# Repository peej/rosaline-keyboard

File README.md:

# Rosaline - Through-hole 40% keyboard PCB for 60% cases

Rosaline is a 40% keyboard PCB using through-hole components for that visible component aesthetic.

The goal of this project is to build an all through-hole component 40% PCB that fits in a standard 60% tray mount case.

Inspired by the [Plaid](https://github.com/hsgw/plaid) and the [Romeo](https://github.com/coseyfannitutti/romeo).

* Designed to be easy to build with minimal soldering experience.
* All through-hole components, no SMD soldering required.
* Get that visible component aesthetic in a standard 60% tray-mount case.
* Staggered and ortholinear varieties.
* Supports both USB Mini and USB-C.

The layout is a number row-less 60% layout with split spacebar or 7u bottom row and split right shift. An arrow cluster layout is also supported by moving the right shift.

# Ordering parts

PCBs can be manufactuered by a variety of online PCB fabricators. You can use [PCBShopper](https://pcbshopper.com/) to search for the best price.

# Construction

Solder all the components onto the top side of the PCB except the USB connector which should be on the back of the board. Leave the larger components until last so that the board will lie flat upsidedown while you solder the resistors and capacitors.

Take care to put the correct value resistors and capacitors in the correct places, the values are written on the silkmask along with the component reference. If you are unsure about the value of a resistor, check it with a multimeter.

Ensure that polarised components (diodes, LEDs, electrolytic capacitor (C3), IC socket) are in the correct orientation. The square pad is for the negative side of the component; for a diode this means the side with the black stripe; for LEDs and C3 the short leg is the cathode and goes in the square pad.

# Firmware

Firmware has not been merged into QMK upstream as of yet.

## Matrix information

If you are building your own firmware, the following matrix information will be useful to you:

| Configuration   | Value                                  |
|-----------------|----------------------------------------|
| MATRIX_ROWS     | 7                                      |
| MATRIX_COLS     | 8                                      |
| MATRIX_ROW_PINS | C0, B5, B4, B3, B2, B1, C3             |
| MATRIX_COL_PINS | B0, D7, D6, C2, D4, D1, D0, C1         |
| DIODE_DIRECTION | COL2ROW                                |

# Component cover

Cut a piece of 2mm thick acrylic to size (285x19mm) and drill 3 m2 holes for the standoffs. Use the PCB as a guide for the hole positions.

Affix the 3 standoffs to the PCB with screws from underneath the PCB. Use the remaining 3 screws to attach the acrylic to the top of the standoffs.

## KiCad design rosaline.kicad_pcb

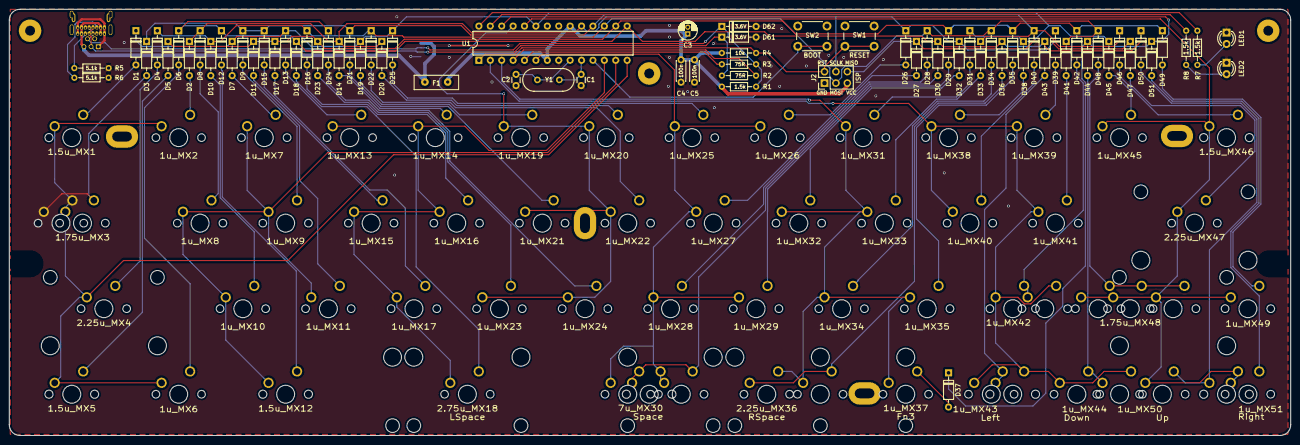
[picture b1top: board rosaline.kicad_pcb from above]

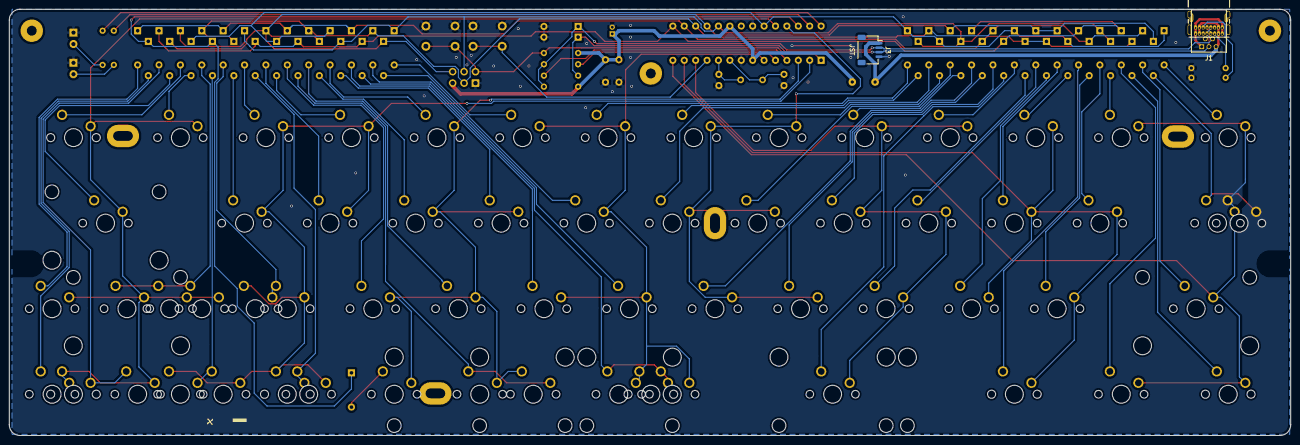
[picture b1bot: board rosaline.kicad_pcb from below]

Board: 2 copper layers, 285.4 x 94.9 mm, 148 parts (3 on the bottom side), 83 nets.

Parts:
1.5u_MX1: Tab; MX_PCB_150H
1.5u_MX5: LCtrl; MX_PCB_150H
1.5u_MX12: LAlt; MX_PCB_150H
1.5u_MX43: RAlt; MX_PCB_150H
1.5u_MX46: Back; MX_PCB_150H
1.5u_MX50: RCtrl; MX_PCB_150H
1.75u_MX3: Esc; MX_PCB_175H
1.75u_MX42, 1.75u_MX48: RShift; MX_PCB_175H
1u2_MX44: RGui; MX
1u_MX2: Q; MX
1u_MX6: LGui; MX
1u_MX7: W; MX
1u_MX8: A; MX
1u_MX9: S; MX
1u_MX10: Z; MX
1u_MX11: X; MX
1u_MX13: E; MX
1u_MX14: R; MX
1u_MX15: D; MX
1u_MX16, 1u_MX21: F; MX
1u_MX17: C; MX
1u_MX19: T; MX
1u_MX20: Y; MX
1u_MX22: G; MX
1u_MX23: V; MX
1u_MX24: B; MX
1u_MX25: U; MX
1u_MX26: I; MX
1u_MX27: J; MX
1u_MX28: N; MX
1u_MX29: M; MX
1u_MX30, 1u_MX36: Fn2; MX
1u_MX31: O; MX
1u_MX32: K; MX
1u_MX33: L; MX
1u_MX34: ,; MX
1u_MX35: .; MX
1u_MX37: Fn3; MX
1u_MX38: P; MX
1u_MX39: [; MX
1u_MX40: ;; MX
1u_MX41: '; MX
1u_MX42: /; MX
1u_MX43: Left; MX
1u_MX44: Down; MX
1u_MX45: ]; MX
1u_MX48, 1u_MX50: Up; MX
1u_MX49: Fn; MX
1u_MX51: Right; MX
2.25u_MX4: LShift; MX_PCB_225H
2.25u_MX30, 2.25u_MX36: RSpace; MX_PCB_225B
2.25u_MX47: Enter; MX_PCB_225H
2.75u_MX18: LSpace; MX_PCB_275B
2.75u_MX48: RShift; MX_PCB_275H
7u_MX30: Space; MX_PCB_700H
C1, C2: 22p; C_Disc_D3.0mm_W1.6mm_P2.50mm
C3: 4.7u; CP_Radial_D4.0mm_P1.50mm
C4, C5: 100n; C_Disc_D4.3mm_W1.9mm_P5.00mm
D1, D2, D3, D4, D5, D6, D7, D8, D9, D10, D11, D12, D13, D14, D15, D16, D17, D18, D19, D20, D21, D22, D23, D24, D25, D26, D27, D28, D29, D30, D31, D32, D33, D34, D35, D36, D37, D38, D39, D40, D41, D42, D43, D44, D45, D46, D47, D48, D49, D50, D51: 1N4148; D_DO-35_SOD27_P7.62mm_Horizontal
D61, D62: 3.6V; D_DO-35_SOD27_P7.62mm_Horizontal
F1: 100mA; Fuse_Bourns_MF-RHT100
Flags: flags; Flags
H1, H2, H3: M2; MountingHole_M2
H4, H9: M2; MountingSlot_M2
H5, H6, H7, H8: M2; MountingFlex_M2
J1: USB; USB_Hybrid_THT
J2: AVR_ISP_6; PinHeader_2x03_P2.54mm_Vertical
J3: JST; JST_SH_SM04B-SRSS-TB_1x04-1MP_P1.00mm_Horizontal
LED1: RED; LED_D3.0mm
LED2: GREEN; LED_D3.0mm
OSHW: OSHW-Logo_7.5x8mm_Copper
R1, R7, R8: 1.5k; R_Axial_DIN0204_L3.6mm_D1.6mm_P7.62mm_Horizontal
R2, R3: 75R; R_Axial_DIN0204_L3.6mm_D1.6mm_P7.62mm_Horizontal
R4: 10k; R_Axial_DIN0204_L3.6mm_D1.6mm_P7.62mm_Horizontal
R5, R6: 5.1k; R_Axial_DIN0204_L3.6mm_D1.6mm_P7.62mm_Horizontal
SW1: RESET; SW_PUSH_6mm
SW2: BOOT; SW_PUSH_6mm
U1: ATMEGA328-PU; DIP-28_W7.62mm
Y1: 16MHz; Crystal_HC49-4H_Vertical
stepped_MX3: Esc; MX

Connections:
+5V: C3.1, C4.1, C5.1, F1.2, J2.5, R1.2, R4.1, U1.7, U1.20
/COL0: 1.5u_MX1.2, 1.5u_MX5.2, 1.75u_MX3.2, 1u_MX2.2, 1u_MX6.2, 2.25u_MX4.2, U1.14, stepped_MX3.1
/COL1: 1.5u_MX12.2, 1u_MX7.2, 1u_MX8.2, 1u_MX9.2, 1u_MX10.2, 1u_MX11.2, U1.13
/COL2: 1u_MX13.2, 1u_MX14.2, 1u_MX15.2, 1u_MX16.2, 1u_MX17.2, 2.75u_MX18.2, U1.12
/COL3: 1u_MX19.2, 1u_MX20.2, 1u_MX21.2, 1u_MX22.2, 1u_MX23.2, 1u_MX24.2, U1.25
/COL4: 1u_MX25.2, 1u_MX26.2, 1u_MX27.2, 1u_MX28.2, 1u_MX29.2, 1u_MX30.2, 2.25u_MX30.2, 7u_MX30.1, U1.6
/COL5: 1u_MX31.2, 1u_MX32.2, 1u_MX33.2, 1u_MX34.2, 1u_MX35.2, 1u_MX36.2, 1u_MX37.2, 2.25u_MX36.1, U1.3
/COL6: 1.5u_MX43.1, 1.75u_MX42.1, 1u2_MX44.1, 1u_MX38.2, 1u_MX39.2, 1u_MX40.2, 1u_MX41.2, 1u_MX42.2, 1u_MX43.2, 1u_MX44.2, U1.2
/COL7: 1.5u_MX46.2, 1.5u_MX50.1, 1.75u_MX48.2, 1u_MX45.2, 1u_MX48.2, 1u_MX49.2, 1u_MX50.2, 1u_MX51.2, 2.25u_MX47.2, 2.75u_MX48.2, U1.24
/LED1: R7.1, U1.28
/LED2: R8.1, U1.27
/RESET: J2.2, R4.2, SW1.1, U1.1
/ROW0: D1.1, D7.1, D13.1, D19.1, D25.1, D31.1, D38.1, D45.1, U1.23
/ROW1: D2.1, D8.1, D14.1, D20.1, D26.1, D32.1, D39.1, D46.1, J2.4, U1.19
/ROW2: D3.1, D9.1, D15.1, D21.1, D27.1, D33.1, D40.1, D47.1, J2.6, U1.18
/ROW3: D4.1, D10.1, D16.1, D22.1, D28.1, D34.1, D41.1, D48.1, J2.3, U1.17
/ROW4: D5.1, D11.1, D17.1, D23.1, D29.1, D35.1, D42.1, D49.1, U1.16
/ROW5: D6.1, D12.1, D18.1, D24.1, D30.1, D36.1, D43.1, D50.1, U1.15
/ROW6: D37.1, D44.1, D51.1, U1.26
/USB_D+: R2.2, U1.4
/USB_D-: R3.2, U1.5
GND: C1.2, C2.2, C3.2, C4.2, C5.2, D61.2, D62.2, J1.GND, J2.1, J3.4, LED1.1, LED2.1, R5.1, R6.1, SW1.2, SW2.2, U1.8, U1.22
unnamed: 1.5u_MX1.1, D1.2
unnamed: 1.5u_MX5.1, D5.2
unnamed: 1.5u_MX12.1, D12.2
unnamed: 1.5u_MX43.2, 1u_MX43.1, D43.2
unnamed: 1.5u_MX46.1, D46.2
unnamed: 1.5u_MX50.2, 1u_MX50.1, D50.2
unnamed: 1.75u_MX3.1, D3.2, stepped_MX3.2
unnamed: 1.75u_MX42.2, 1u_MX42.1, D42.2
unnamed: 1.75u_MX48.1, 1u_MX48.1, 2.75u_MX48.1, D48.2
unnamed: 1u2_MX44.2, 1u_MX44.1, D44.2
unnamed: 1u_MX2.1, D2.2
unnamed: 1u_MX6.1, D6.2
unnamed: 1u_MX7.1, D7.2
unnamed: 1u_MX8.1, D8.2
unnamed: 1u_MX9.1, D9.2
unnamed: 1u_MX10.1, D10.2
unnamed: 1u_MX11.1, D11.2
unnamed: 1u_MX13.1, D13.2
unnamed: 1u_MX14.1, D14.2
unnamed: 1u_MX15.1, D15.2
unnamed: 1u_MX16.1, D16.2
unnamed: 1u_MX17.1, D17.2
unnamed: 1u_MX19.1, D19.2
unnamed: 1u_MX20.1, D20.2
unnamed: 1u_MX21.1, D21.2
unnamed: 1u_MX22.1, D22.2
unnamed: 1u_MX23.1, D23.2
unnamed: 1u_MX24.1, D24.2
unnamed: 1u_MX25.1, D25.2
unnamed: 1u_MX26.1, D26.2
unnamed: 1u_MX27.1, D27.2
unnamed: 1u_MX28.1, D28.2
unnamed: 1u_MX29.1, D29.2
unnamed: 1u_MX30.1, 2.25u_MX30.1, 7u_MX30.2, D30.2
unnamed: 1u_MX31.1, D31.2
unnamed: 1u_MX32.1, D32.2
unnamed: 1u_MX33.1, D33.2
unnamed: 1u_MX34.1, D34.2
unnamed: 1u_MX35.1, D35.2
unnamed: 1u_MX36.1, 2.25u_MX36.2, D36.2
unnamed: 1u_MX37.1, D37.2
unnamed: 1u_MX38.1, D38.2
unnamed: 1u_MX39.1, D39.2
unnamed: 1u_MX40.1, D40.2
unnamed: 1u_MX41.1, D41.2
unnamed: 1u_MX45.1, D45.2
unnamed: 1u_MX49.1, D49.2
unnamed: 1u_MX51.1, D51.2
unnamed: 2.25u_MX4.1, D4.2
unnamed: 2.25u_MX47.1, D47.2
unnamed: 2.75u_MX18.1, D18.2
unnamed: C1.1, U1.10, Y1.2
unnamed: C2.1, U1.9, Y1.1
unnamed: D61.1, J1.D+, J3.3, R2.1
unnamed: D62.1, J1.D-, J3.2, R1.1, R3.1
unnamed: F1.1, J1.V+, J3.1
unnamed: J1.CC1, R5.2
unnamed: J1.CC2, R6.2
unnamed: LED1.2, R7.2
unnamed: LED2.2, R8.2
unnamed: SW2.1, U1.11

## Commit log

2021-05-24 Add documentation
2021-05-26 Change bottom row layout options
2021-05-27 Add component cover DXF
2021-07-31 Switch bottom row stabilizer orientation
2021-08-12 Add plate
2021-08-12 Add ortho variant
2021-08-12 Add ortho layout to readme
2021-08-12 Add gerber files
2021-08-12 Fix exported cover DXF file
2021-08-20 Fix overlapping trace on MX30
2021-08-20 Add fmask layer to ortho plate
2021-08-31 Rename project
2021-09-01 Update PCB renders
2021-09-01 Update plate files
2021-09-01 Fix broken trace on ortho PCB
2021-09-30 Add stepped caps lock switch footprint
2021-10-10 Remove ortholinear layout information from README
